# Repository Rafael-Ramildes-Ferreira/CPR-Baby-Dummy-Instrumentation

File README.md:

# CPR-Baby-Dummy-Instrumentation
The goal is to apply sensors to verify CPR training on a Baby dummy. This is part of curse of Projeto Integrador (DAS5104) in UFSC, 2024, 1st semester.

The prject started at 2023/2 and the code made that semester can be seen [here](https://github.com/PSCoes/Projeto_Integrador).

The ESP code was developed using [Platform.io](https://platformio.org)

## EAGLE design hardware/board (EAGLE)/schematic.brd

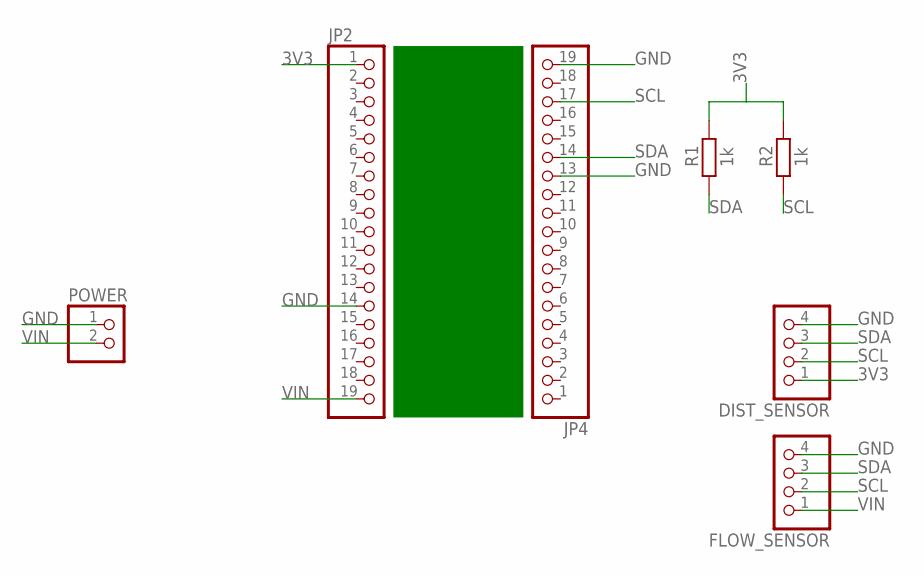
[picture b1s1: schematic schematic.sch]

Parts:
DIST_SENSOR: PINHD-1X4; 1X04
FLOW_SENSOR: PINHD-1X4; 1X04
JP2, JP4: PINHD-1X19; 1X19
POWER: PINHD-1X2; 1X02
R1, R2: 1k; 0207/10

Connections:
3V3: DIST_SENSOR.1, JP2.1, R1.2, R2.2
GND: DIST_SENSOR.4, FLOW_SENSOR.4, JP2.14, JP4.13, JP4.19, POWER.1
SCL: DIST_SENSOR.3, FLOW_SENSOR.3, JP4.17, R2.1
SDA: DIST_SENSOR.2, FLOW_SENSOR.2, JP4.14, R1.1
VIN: FLOW_SENSOR.1, JP2.19, POWER.2

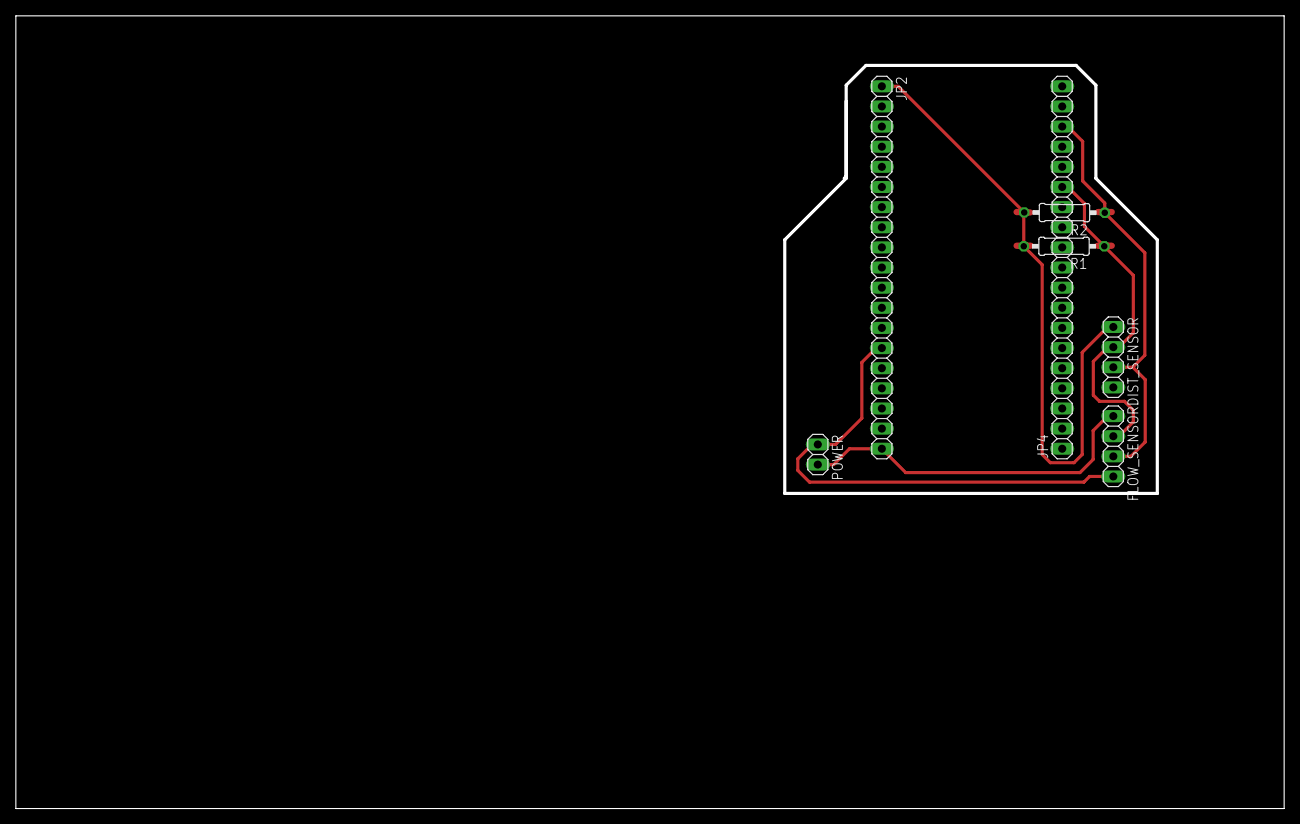
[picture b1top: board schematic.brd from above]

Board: 2 copper layers, 160.0 x 100.0 mm, 7 parts (0 on the bottom side), 5 nets.

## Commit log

2024-04-08 Update README.md
    Very Basic README done
2024-04-08 Add: Platform.io project created
2024-04-08 Add: Distance sensor library included and sensor initialization
2024-04-08 Add: Sensor read function
2024-04-08 Fix: Ignores failed sensor readings
2024-04-09 Add: function to calculate the frequency
2024-04-09 Functions reorganized in different files
2024-04-09 Add: Find peak function implementation
2024-04-15 Add: Last valley implementation and some debugging printing
2024-04-15 Add: Timer interrupt to send wireles signals
2024-04-15 Add: buildconfig header file
2024-04-15 Add: Version information on library dependances on platformio.ini
2024-04-16 WatchDog is working as expected - WE NEED TO TEST THE DISTANCE SENSOR
2024-04-16 Add: wifi conection. It can already be conected
2024-04-16 Add: Timer interrupt configuration generalized to be used with wifi and bluetooth
2024-04-17 Useless code clean up and comments added
2024-04-17 Chest compression turneded into a class
2024-04-17 Statistics turned into utils turned into a class
2024-04-17 Fix: Now it expects ChestCompression to be a class
2024-04-17 Fix: Wifi communicator turned into a class
2024-04-17 Fix: Timer Interrupt clas created to wrap ESP8266 ITimer class
2024-04-17 Fix: Setting of ssid
2024-04-22 Deviation threshold configured (tests ceased due to sensor not conecting - maybe because of the wirering?)
2024-04-22 Fix: Integration fixes and ChestCompression Getters defined
2024-05-14 Add: Libdependance of SFMxx and sets up a test for the SFM3400
2024-05-26 platformio.ini configured to use NodeMCU ESP32s
2024-05-27 Gets rid of the watchdog reset calls
2024-05-27 Configures time interruption to the NodeMCU EPS32
2024-05-27 Wireless communicator class adapted to ESP 32s
2024-05-27 Now WiFi communicator is completely static
2024-05-27 Chest is initiated inside setup, so now it works!
2024-05-28 Uncomment the wifi module initialization
2024-05-28 Add: Air sensor class
2024-05-29 May 29th, 2024: Still under testing, Stopped reading VL6180, added a I2C scanner that confirmed the expected IDs
2024-05-29 I2C_Scanner.cpp moved to new directory ´utils´, since ´test´ is for test codes
    And news: I can't communicate with VL6180X with the example library code neither
2024-05-29 Distance sensor readings ´fixed´ (in a hacky way)
2024-06-03 No longer yields communication error
2024-06-03 Tested and it worked
2024-06-03 Debug flag is now actually used in code
2024-06-03 Unnecessaries includes trimed, It is not seting up the timer interrupt
2024-06-04 Configured to interrupt, but it's pinicing
2024-06-04 Interrupt seems to be fixed
2024-06-13 No longer initializing the communicator with nullptrs
    request_to_send moved to a variable, maybe revert this later
2024-06-13 Tested and transmitting through WiFi, printings deleted, not reading right
2024-06-17 Dist Sensor readings review, printing error code when DEBUG flag is defined
2024-06-18 Calculates the distance and frequency every time get_distance and get_frequency gets called
2024-06-18 Old implementation of timer interrupt deleted and a idea of ISR change was added
2024-06-18 request_to_send became part of the class again and measurements of the sensors are made before start the Wi-Fi transmission
2024-06-18 In send wifi function, Serial.println moved after the WiFi transmission
2024-06-19 Blutooth communicator class written
2024-06-22 Configured to run with Bluetooth
2024-06-22 Compilation problems fixed
2024-06-26 Bluetooth funcionando, sensor de fluxo desconectado pois queimou
2024-07-02 Adds flag for defining if frequency is to be calculated on ESP
2024-07-02 Added peak finder code that was previously tested on Arduíno IDE
2024-07-03 Frequency calculation that was previously tested on Arduino IDE brought to Platformio
2024-07-03 Repeated code removed
2024-07-03 Fix mistakes during confict resolutions
2024-07-03 Bluetooth notifications are activated and validated
2024-07-03 Parameters tested in Arduino IDE brought to Platform.io (I forgot to bring'em earlier
2024-07-03 Configured to send frequency through Bluetooth
2024-07-03 Debug printing fixed
2024-07-03 Bluetooth updates are now called by ISR
2024-07-05 Revert "Bluetooth updates are now called by ISR"
    This reverts commit 139edabfa6c8350be81523d6a431ee11ffcf9e10.
2024-07-05 Feeding the watchdog more often and not calculating the frequency in get_frequency
2024-07-05 Air flow class operation standardized
    It now has a I2C reading method - readFlow() - and a stored value get method - get_flow()
    So it now has to store the value
    It was also added to the main.c code
2024-07-05 Using flags to activate and deactivate the usage of sensors
2024-07-05 Sending both distance and frequency reliably, now it only sends if something is conected
2024-07-08 Bluetooth class no longer use so many statics
2024-07-08 Making frequency decrease over time
2024-07-08 Makes sure to start advertizing again after a disconnect and that the led is turned off when disconnected
    The advertiziment thing seems to have helped with reconnecting with nRF Connect after a disconnection
2024-07-09 New frequency calculation algorithm working
2024-07-09 Never coment the DEBUG flag :)
2024-07-09 Added Eagle's board file
2024-07-09 Added the air flow sensor conector clip
2024-07-09 I don't know why there was a BLE example inside the repository
2024-07-09 Mensions platform.io in README.md
2024-10-31 Blobing hello world (both with Serial.println and with printf)
2024-11-04 Adds R2U2 and compiles
    - Pointers to arrays with specified size in the default monitor had to be reinterpreted as pointers to array of unspecified size to fit the monitor structure
    - C and C plus plus version had to be specified
    - C version check done in config.h was adapted to expect compatible C++
2024-11-06 Initial instruction memory linking test
2024-11-07 Make a feasible sized monitor structure and move specifications to .rodata
2024-11-11 Make a class to deal with the monitor
2024-11-12 Includes R2U2 with a not deprecated method
2024-11-12 Configures the monitor upon the start of the execution
2024-11-13 Makes a functional allocation of the monitor struct and makes the monitor run (giving wrong results yet)
2024-11-18 Allocates both box queue and share connection queue (still wrong verdicts)
2024-11-19 Appears to be working with the hacky solution of changing op->value to op->value-1 in R2U2_FT_OP_SUBFORMULA at past_time::get_operand
2024-11-22 Fix paddin issues with instruction structure: malloc is no longer needed and the program doesn't crash when there are more tha one requirement
    - It still gives the same result for both expressions when it shouldn't. Issue: Fix duplicated results
    - malloc is still used for the signal vectors (I don't know of a nother way) Issue: Verify correct way of allocating space for signal vector
    - I haven't checked if other paddings ware causing problems. I should check all relevant structures
    malloc for boxq and scq are no longer needed since the space for this structures are alocated during the monitor initialization, the padding difference from Linux to ESP32 ware causing mismatches tha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
2024-11-23 Monitor memory allocation settings repositioned to new file
2024-11-23 Fix requirement tag printing in the out_func, plus configure it to run with floats
    - Still only returns one of the requirements correctly
2024-11-23 Changes the comment at the begining of the main file for documentation
    Meanwhile changes ware made to R2U2 lib so it would work on ESP32:
    ### Padding
    Paddings ware added to structures to combat differences in memory alignment. These structures are:
    - 2u2_mltl_instruction_t
    - 2u2_boxq_t
    - 2u2_instruction_t
2024-11-23 Add documentation file for the usage of R2U2 and remove old and useless files
2024-11-23 Documentation formatting fix
2024-11-24 Moves sizes definition to inside the internals/bounds.h in R2U2 library
2024-11-24 Fix float variable initialization (allocing the right size)
2024-11-25 Add pading to monitor (padding in the arrays are yet weird)
2024-11-25 Quality of life improvement on enabling and disabling sensors
2024-11-25 Adds the possibility of configuring two timer interrupts
2024-11-25 Adds a second timer interrupt to export the trace
2024-11-25 Fix time stamp (it wasn't being incremented) and configures to run, trace data was collected
2024-11-25 Funcionando para a apresentação
2024-11-25 Working with both monitors!!!!!
2024-12-04 Added a third specification: O[0,3] send
2024-12-04 Keeps the class even when the sensor is disable to help with the RV
